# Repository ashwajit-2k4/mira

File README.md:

### EDL 2025 Project Submission Repository.

### Project Name: P-05 : Magnetic Field Camera
### Team Number: MON-08
### Team Members:
- Aditya Vema Reddy Kesari (22b3985)
- Ashwajit Singh (22b1227)
- N V Navaneeth Rajesh (22b1215)
- Raunak Mukherjee (22b3955)
- Suchet Gopal (22b1814)

### Problem Statement and Solution:

<!-- Provide a description about the project and what you've learnt and achieved in this. -->

<b> Problem Statement </b> 

High resolution magnetic imaging of objects is extremely important in industrial applications, to check for defects in manufactured parts like permanent magnets or motors. However, many current products like MAGCAM have exhorbitant costs that make them unviable for many people.

<b> Our Solution </b> 

MIRA M1 fills in this gap, as an affordable  magnetic field camera consisting of an 8x8 sensor array, that maps the field distribution in the volume around an object using an r-theta-z movement rig in just a few minutes. 

The object to be measured is placed on a rotating platform, with the sensor array itself moving in the r-z plane, thus enabling the mapping out of 3D space. The user interacts with a laptop-based GUI, to move the sensors to the starting position, and then start the pre-programmed sweep. The GUI then shows the live heatmap of the values the sensor array sees (at above 80 frames per second), along with a continuously updating scatter plot showing a 3D visualisation of the field.

<b> How It Works </b> 

The GUI starts an SSH connection to a Raspberry Pi, that controls the motors for rig movement, and communicates with the CMOD A7 FPGA that interfaces with the sensor array. When acquisition is started, the RPi rotates the theta motor by 360 degrees in 200 steps, acquiring data from sensors in every step. It then moves in the r direction in steps, repeating this process before it moves up in the z direction.

<b> Deliverables </b> 

- 2mm spatial resolution: **Achieved** (Currently with 1.75mm resolution, which can be increased further)
- 1mT sensitivity: **Achieved** (Obtained 0.2mT sensitivity)

### Key Learnings

Since our project had a lot of moving parts, with the CMOD FPGA, the Raspberry Pi microcontroller and the laptop GUI, in addition to the motor movement mechanism, communication was essential to ensure compatibility between these parts. Additionally, we had to put a lot of thought into component choice, since we could not use commonly available steel components due to interference. Since we required very high resolution, both in terms of magnetic field and spatial movement, it required careful design of PCBs and CAD models, and required adapting parts in the mechanism to ensure that we had minimum spatial error from jitter.

### Walkthrough of the repo

The source code consists of code for 3 devices: CMOD A7 FPGA, Raspberry Pi 5 and the laptop GUI. Additionally, the PCB designs for the sensor PCB we ultimately used, along with the backup PCB, and the PCB containing the FPGA are provided. The CAD models for all 3D printed and laser cut parts are also provided.

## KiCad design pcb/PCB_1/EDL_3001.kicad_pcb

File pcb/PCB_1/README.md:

# TMAG3001 Sensor Array PCB

This repository contains the design files and documentation for the **TMAG3001 Sensor Array PCB**. This is the **main PCB** of the project, designed for high-resolution magnetic field sensing using a dense grid of magnetometers.

## Overview

- **Sensor Type**: TMAG3001 3-axis magnetometers  
- **Array Size**: 8x8 grid (64 sensors)  
- **Inter-sensor Spacing**: 3.5 mm  
- **PCB Type**: 4-layer board  
- **Communication Protocol**: I2C  

---

## Design Details

### I2C Bus Structure

Each group of **4 sensors** forms a **single I2C bus**.  
- Each **TMAG3001** uses **3 I2C lines**: `SCL`, `SDA`, and `INT`.
- A single bus handles 4 sensors, with address selection via the `ADD` pin.
- The `ADD` pin is tied to one of: `VCC`, `GND`, `SCL`, or `SDA` — enabling 4 unique addresses per bus.

> **Note**: To reduce the number of GPIOs, the `INT` lines from every **2 buses are shorted** together.

### Electrical Components

- **Pull-up Resistors**: 1.8 kΩ on all I2C lines  
- **Decoupling Capacitors**:
  - 0.1 µF per IC
  - 2 × 1 µF bulk capacitors at the power input  
- **Power Supply Pins** (per IC): `VCC`, `GND`, `INT`, `SCL`, `SDA`, `ADD`

### Physical Layout

- **IC Placement**: Only TMAG3001 ICs are placed on the **top** layer to avoid magnetic interference.
- **Other Components**: All resistors, capacitors, connectors, etc., are placed on the **bottom** layer.
- **Test Points**: 10 test points on the **bottom** for signal probing and ground testing.

### Grounding and Layer Design

- All 4 layers have **solid ground pours** for noise suppression and signal integrity.

---

## Files & Resources

The repository folders include:
- **Schematic**
- **PCB Layout**
- **3D Renders**
- **Assembled PCB Images**

---

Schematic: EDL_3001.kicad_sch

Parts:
C1, C2, C3, C4, C5, C6, C7, C8, C9, C10, C11, C12, C13, C14, C15, C16, C17, C18, C19, C20, C21, C22, C23, C24, C25, C26, C27, C28, C29, C30, C31, C32, C33, C34, C35, C36, C37, C38, C39, C40, C41, C42, C43, C44, C45, C46, C47, C48, C49, C50, C51, C52, C53, C54, C55, C56, C57, C58, C59, C60, C61, C62, C63, C64: 0.1 u; C_0402_1005Metric
C65, C66: 1 u; C_1206_3216Metric
J1, J2: 524353071; 52435-3071
R1, R2, R3, R4, R5, R6, R7, R8, R9, R10, R11, R12, R13, R14, R15, R16, R17, R18, R19, R20, R21, R22, R23, R24, R25, R26, R27, R28, R29, R30, R31, R32, R33, R34, R35, R36, R37, R38, R39, R40, R41, R42, R43, R44, R45, R46, R47, R48: 1.8k; R_0402_1005Metric
TP1, TP2, TP3, TP4, TP5, TP6, TP7, TP8, TP9, TP10: TestPoint; TestPoint_Plated_Hole_D2.0mm
U1, U2, U3, U4, U5, U6, U7, U8, U9, U10, U11, U12, U13, U14, U15, U16, U17, U18, U19, U20, U21, U22, U23, U24, U25, U26, U27, U28, U29, U30, U31, U32, U33, U34, U35, U36, U37, U38, U39, U40, U41, U42, U43, U44, U45, U46, U47, U48, U49, U50, U51, U52, U53, U54, U55, U56, U57, U58, U59, U60, U61, U62, U63, U64: TMAG3001A2YBGR; DSBGA6_YBG_TEX

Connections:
GND: C1.2, C2.2, C3.2, C4.2, C5.2, C6.2, C7.2, C8.2, C9.2, C10.2, C11.2, C12.2, C13.2, C14.2, C15.2, C16.2, C17.2, C18.2, C19.2, C20.2, C21.2, C22.2, C23.2, C24.2, C25.2, C26.2, C27.2, C28.2, C29.2, C30.2, C31.2, C32.2, C33.2, C34.2, C35.2, C36.2, C37.2, C38.2, C39.2, C40.2, C41.2, C42.2, C43.2, C44.2, C45.2, C46.2, C47.2, C48.2, C49.2, C50.2, C51.2, C52.2, C53.2, C54.2, C55.2, C56.2, C57.2, C58.2, C59.2, C60.2, C61.2, C62.2, C63.2, C64.2, C65.2, C66.2, J1.1, J1.2, J1.3, J1.4, J1.5, J1.6, J1.7, J1.8, J1.9, J1.10, J1.31, J1.32, J2.21, J2.22, J2.23, J2.24, J2.25, J2.27, J2.29, J2.30, J2.31, J2.32, TP9.1, TP10.1, U1.B2 (GND), U2.A2 (ADDR), U2.B2 (GND), U3.B2 (GND), U4.B2 (GND), U5.B2 (GND), U6.A2 (ADDR), U6.B2 (GND), U7.B2 (GND), U8.B2 (GND), U9.B2 (GND), U10.A2 (ADDR), U10.B2 (GND), U11.B2 (GND), U12.B2 (GND), U13.B2 (GND), U14.A2 (ADDR), U14.B2 (GND), U15.B2 (GND), U16.B2 (GND), U17.B2 (GND), U18.A2 (ADDR), U18.B2 (GND), U19.B2 (GND), U20.B2 (GND), U21.B2 (GND), U22.A2 (ADDR), U22.B2 (GND), U23.B2 (GND), U24.B2 (GND), U25.B2 (GND), U26.A2 (ADDR), U26.B2 (GND), U27.B2 (GND), U28.B2 (GND), U29.B2 (GND), U30.A2 (ADDR), U30.B2 (GND), U31.B2 (GND), U32.B2 (GND), U33.B2 (GND), U34.A2 (ADDR), U34.B2 (GND), U35.B2 (GND), U36.B2 (GND), U37.B2 (GND), U38.A2 (ADDR), U38.B2 (GND), U39.B2 (GND), U40.B2 (GND), U41.B2 (GND), U42.A2 (ADDR), U42.B2 (GND), U43.B2 (GND), U44.B2 (GND), U45.B2 (GND), U46.A2 (ADDR), U46.B2 (GND), U47.B2 (GND), U48.B2 (GND), U49.B2 (GND), U50.A2 (ADDR), U50.B2 (GND), U51.B2 (GND), U52.B2 (GND), U53.B2 (GND), U54.A2 (ADDR), U54.B2 (GND), U55.B2 (GND), U56.B2 (GND), U57.B2 (GND), U58.A2 (ADDR), U58.B2 (GND), U59.B2 (GND), U60.B2 (GND), U61.B2 (GND), U62.A2 (ADDR), U62.B2 (GND), U63.B2 (GND), U64.B2 (GND)
unnamed: R33.2, R34.1
unnamed: R35.2, R36.1
unnamed: R37.2, R38.1
unnamed: R39.2, R40.1
unnamed: R41.2, R42.1
unnamed: R43.2, R44.1
unnamed: R45.2, R46.1
unnamed: R47.2, R48.1
unnamed: J1.30, R34.2, U1.B1 (*INT), U2.B1 (*INT), U3.B1 (*INT), U4.B1 (*INT), U5.B1 (*INT), U6.B1 (*INT), U7.B1 (*INT), U8.B1 (*INT)
unnamed: J1.29, R1.2, U1.C2 (SCL), U2.C2 (SCL), U3.C2 (SCL), U4.A2 (ADDR), U4.C2 (SCL)
unnamed: J1.28, R2.2, U1.C1 (SDA), U2.C1 (SDA), U3.A2 (ADDR), U3.C1 (SDA), U4.C1 (SDA)
unnamed: J1.27, R3.2, U5.C2 (SCL), U6.C2 (SCL), U7.C2 (SCL), U8.A2 (ADDR), U8.C2 (SCL)
unnamed: J1.26, R4.2, U5.C1 (SDA), U6.C1 (SDA), U7.A2 (ADDR), U7.C1 (SDA), U8.C1 (SDA)
unnamed: J1.25, R36.2, U9.B1 (*INT), U10.B1 (*INT), U11.B1 (*INT), U12.B1 (*INT), U13.B1 (*INT), U14.B1 (*INT), U15.B1 (*INT), U16.B1 (*INT)
unnamed: J1.24, R5.2, U9.C2 (SCL), U10.C2 (SCL), U11.C2 (SCL), U12.A2 (ADDR), U12.C2 (SCL)
unnamed: J1.23, R6.2, U9.C1 (SDA), U10.C1 (SDA), U11.A2 (ADDR), U11.C1 (SDA), U12.C1 (SDA)
unnamed: J1.22, R7.2, U13.C2 (SCL), U14.C2 (SCL), U15.C2 (SCL), U16.A2 (ADDR), U16.C2 (SCL)
unnamed: J1.21, R8.2, U13.C1 (SDA), U14.C1 (SDA), U15.A2 (ADDR), U15.C1 (SDA), U16.C1 (SDA)
unnamed: J1.20, R38.2, U17.B1 (*INT), U18.B1 (*INT), U19.B1 (*INT), U20.B1 (*INT), U21.B1 (*INT), U22.B1 (*INT), U23.B1 (*INT), U24.B1 (*INT)
unnamed: J1.19, R9.2, U17.C2 (SCL), U18.C2 (SCL), U19.C2 (SCL), U20.A2 (ADDR), U20.C2 (SCL)
unnamed: J1.18, R10.2, U17.C1 (SDA), U18.C1 (SDA), U19.A2 (ADDR), U19.C1 (SDA), U20.C1 (SDA)
unnamed: J1.17, R11.2, U21.C2 (SCL), U22.C2 (SCL), U23.C2 (SCL), U24.A2 (ADDR), U24.C2 (SCL)
unnamed: J1.16, R12.2, U21.C1 (SDA), U22.C1 (SDA), U23.A2 (ADDR), U23.C1 (SDA), U24.C1 (SDA)
unnamed: J1.15, R40.2, TP1.1, U25.B1 (*INT), U26.B1 (*INT), U27.B1 (*INT), U28.B1 (*INT), U29.B1 (*INT), U30.B1 (*INT), U31.B1 (*INT), U32.B1 (*INT)
unnamed: J1.14, R13.2, U25.C2 (SCL), U26.C2 (SCL), U27.C2 (SCL), U28.A2 (ADDR), U28.C2 (SCL)
unnamed: J1.13, R14.2, U25.C1 (SDA), U26.C1 (SDA), U27.A2 (ADDR), U27.C1 (SDA), U28.C1 (SDA)
unnamed: J1.12, R15.2, TP2.1, U29.C2 (SCL), U30.C2 (SCL), U31.C2 (SCL), U32.A2 (ADDR), U32.C2 (SCL)
unnamed: J1.11, R16.2, TP3.1, U29.C1 (SDA), U30.C1 (SDA), U31.A2 (ADDR), U31.C1 (SDA), U32.C1 (SDA)
unnamed: J2.1, R42.2, U33.B1 (*INT), U34.B1 (*INT), U35.B1 (*INT), U36.B1 (*INT), U37.B1 (*INT), U38.B1 (*INT), U39.B1 (*INT), U40.B1 (*INT)
unnamed: J2.2, R17.2, U33.C2 (SCL), U34.C2 (SCL), U35.C2 (SCL), U36.A2 (ADDR), U36.C2 (SCL)
unnamed: J2.3, R18.2, U33.C1 (SDA), U34.C1 (SDA), U35.A2 (ADDR), U35.C1 (SDA), U36.C1 (SDA)
unnamed: J2.4, R19.2, U37.C2 (SCL), U38.C2 (SCL), U39.C2 (SCL), U40.A2 (ADDR), U40.C2 (SCL)
unnamed: J2.5, R20.2, U37.C1 (SDA), U38.C1 (SDA), U39.A2 (ADDR), U39.C1 (SDA), U40.C1 (SDA)
unnamed: J2.6, R44.2, U41.B1 (*INT), U42.B1 (*INT), U43.B1 (*INT), U44.B1 (*INT), U45.B1 (*INT), U46.B1 (*INT), U47.B1 (*INT), U48.B1 (*INT)
unnamed: J2.7, R21.2, U41.C2 (SCL), U42.C2 (SCL), U43.C2 (SCL), U44.A2 (ADDR), U44.C2 (SCL)
unnamed: J2.8, R22.2, U41.C1 (SDA), U42.C1 (SDA), U43.A2 (ADDR), U43.C1 (SDA), U44.C1 (SDA)
unnamed: J2.9, R23.2, U45.C2 (SCL), U46.C2 (SCL), U47.C2 (SCL), U48.A2 (ADDR), U48.C2 (SCL)
unnamed: J2.10, R24.2, U45.C1 (SDA), U46.C1 (SDA), U47.A2 (ADDR), U47.C1 (SDA), U48.C1 (SDA)
unnamed: J2.11, R46.2, U49.B1 (*INT), U50.B1 (*INT), U51.B1 (*INT), U52.B1 (*INT), U53.B1 (*INT), U54.B1 (*INT), U55.B1 (*INT), U56.B1 (*INT)
unnamed: J2.12, R25.2, U49.C2 (SCL), U50.C2 (SCL), U51.C2 (SCL), U52.A2 (ADDR), U52.C2 (SCL)
unnamed: J2.13, R26.2, U49.C1 (SDA), U50.C1 (SDA), U51.A2 (ADDR), U51.C1 (SDA), U52.C1 (SDA)
unnamed: J2.14, R27.2, U53.C2 (SCL), U54.C2 (SCL), U55.C2 (SCL), U56.A2 (ADDR), U56.C2 (SCL)
unnamed: J2.15, R28.2, U53.C1 (SDA), U54.C1 (SDA), U55.A2 (ADDR), U55.C1 (SDA), U56.C1 (SDA)
unnamed: J2.16, R48.2, TP4.1, U57.B1 (*INT), U58.B1 (*INT), U59.B1 (*INT), U60.B1 (*INT), U61.B1 (*INT), U62.B1 (*INT), U63.B1 (*INT), U64.B1 (*INT)
unnamed: J2.17, R29.2, U57.C2 (SCL), U58.C2 (SCL), U59.C2 (SCL), U60.A2 (ADDR), U60.C2 (SCL)
unnamed: J2.18, R30.2, U57.C1 (SDA), U58.C1 (SDA), U59.A2 (ADDR), U59.C1 (SDA), U60.C1 (SDA)
unnamed: J2.19, R31.2, TP5.1, U61.C2 (SCL), U62.C2 (SCL), U63.C2 (SCL), U64.A2 (ADDR), U64.C2 (SCL)
unnamed: J2.20, R32.2, TP6.1, U61.C1 (SDA), U62.C1 (SDA), U63.A2 (ADDR), U63.C1 (SDA), U64.C1 (SDA)
VCC: C1.1, C2.1, C3.1, C4.1, C5.1, C6.1, C7.1, C8.1, C9.1, C10.1, C11.1, C12.1, C13.1, C14.1, C15.1, C16.1, C17.1, C18.1, C19.1, C20.1, C21.1, C22.1, C23.1, C24.1, C25.1, C26.1, C27.1, C28.1, C29.1, C30.1, C31.1, C32.1, C66.1, J2.28, R1.1, R2.1, R3.1, R4.1, R5.1, R6.1, R7.1, R8.1, R9.1, R10.1, R11.1, R12.1, R13.1, R14.1, R15.1, R16.1, R33.1, R35.1, R37.1, R39.1, TP7.1, U1.A1 (VCC), U1.A2 (ADDR), U2.A1 (VCC), U3.A1 (VCC), U4.A1 (VCC), U5.A1 (VCC), U5.A2 (ADDR), U6.A1 (VCC), U7.A1 (VCC), U8.A1 (VCC), U9.A1 (VCC), U9.A2 (ADDR), U10.A1 (VCC), U11.A1 (VCC), U12.A1 (VCC), U13.A1 (VCC), U13.A2 (ADDR), U14.A1 (VCC), U15.A1 (VCC), U16.A1 (VCC), U17.A1 (VCC), U17.A2 (ADDR), U18.A1 (VCC), U19.A1 (VCC), U20.A1 (VCC), U21.A1 (VCC), U21.A2 (ADDR), U22.A1 (VCC), U23.A1 (VCC), U24.A1 (VCC), U25.A1 (VCC), U25.A2 (ADDR), U26.A1 (VCC), U27.A1 (VCC), U28.A1 (VCC), U29.A1 (VCC), U29.A2 (ADDR), U30.A1 (VCC), U31.A1 (VCC), U32.A1 (VCC)
VCC2: C33.1, C34.1, C35.1, C36.1, C37.1, C38.1, C39.1, C40.1, C41.1, C42.1, C43.1, C44.1, C45.1, C46.1, C47.1, C48.1, C49.1, C50.1, C51.1, C52.1, C53.1, C54.1, C55.1, C56.1, C57.1, C58.1, C59.1, C60.1, C61.1, C62.1, C63.1, C64.1, C65.1, J2.26, R17.1, R18.1, R19.1, R20.1, R21.1, R22.1, R23.1, R24.1, R25.1, R26.1, R27.1, R28.1, R29.1, R30.1, R31.1, R32.1, R41.1, R43.1, R45.1, R47.1, TP8.1, U33.A1 (VCC), U33.A2 (ADDR), U34.A1 (VCC), U35.A1 (VCC), U36.A1 (VCC), U37.A1 (VCC), U37.A2 (ADDR), U38.A1 (VCC), U39.A1 (VCC), U40.A1 (VCC), U41.A1 (VCC), U41.A2 (ADDR), U42.A1 (VCC), U43.A1 (VCC), U44.A1 (VCC), U45.A1 (VCC), U45.A2 (ADDR), U46.A1 (VCC), U47.A1 (VCC), U48.A1 (VCC), U49.A1 (VCC), U49.A2 (ADDR), U50.A1 (VCC), U51.A1 (VCC), U52.A1 (VCC), U53.A1 (VCC), U53.A2 (ADDR), U54.A1 (VCC), U55.A1 (VCC), U56.A1 (VCC), U57.A1 (VCC), U57.A2 (ADDR), U58.A1 (VCC), U59.A1 (VCC), U60.A1 (VCC), U61.A1 (VCC), U61.A2 (ADDR), U62.A1 (VCC), U63.A1 (VCC), U64.A1 (VCC)

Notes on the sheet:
MAGNETOMETER ARRAY (8X8)
Power Supply

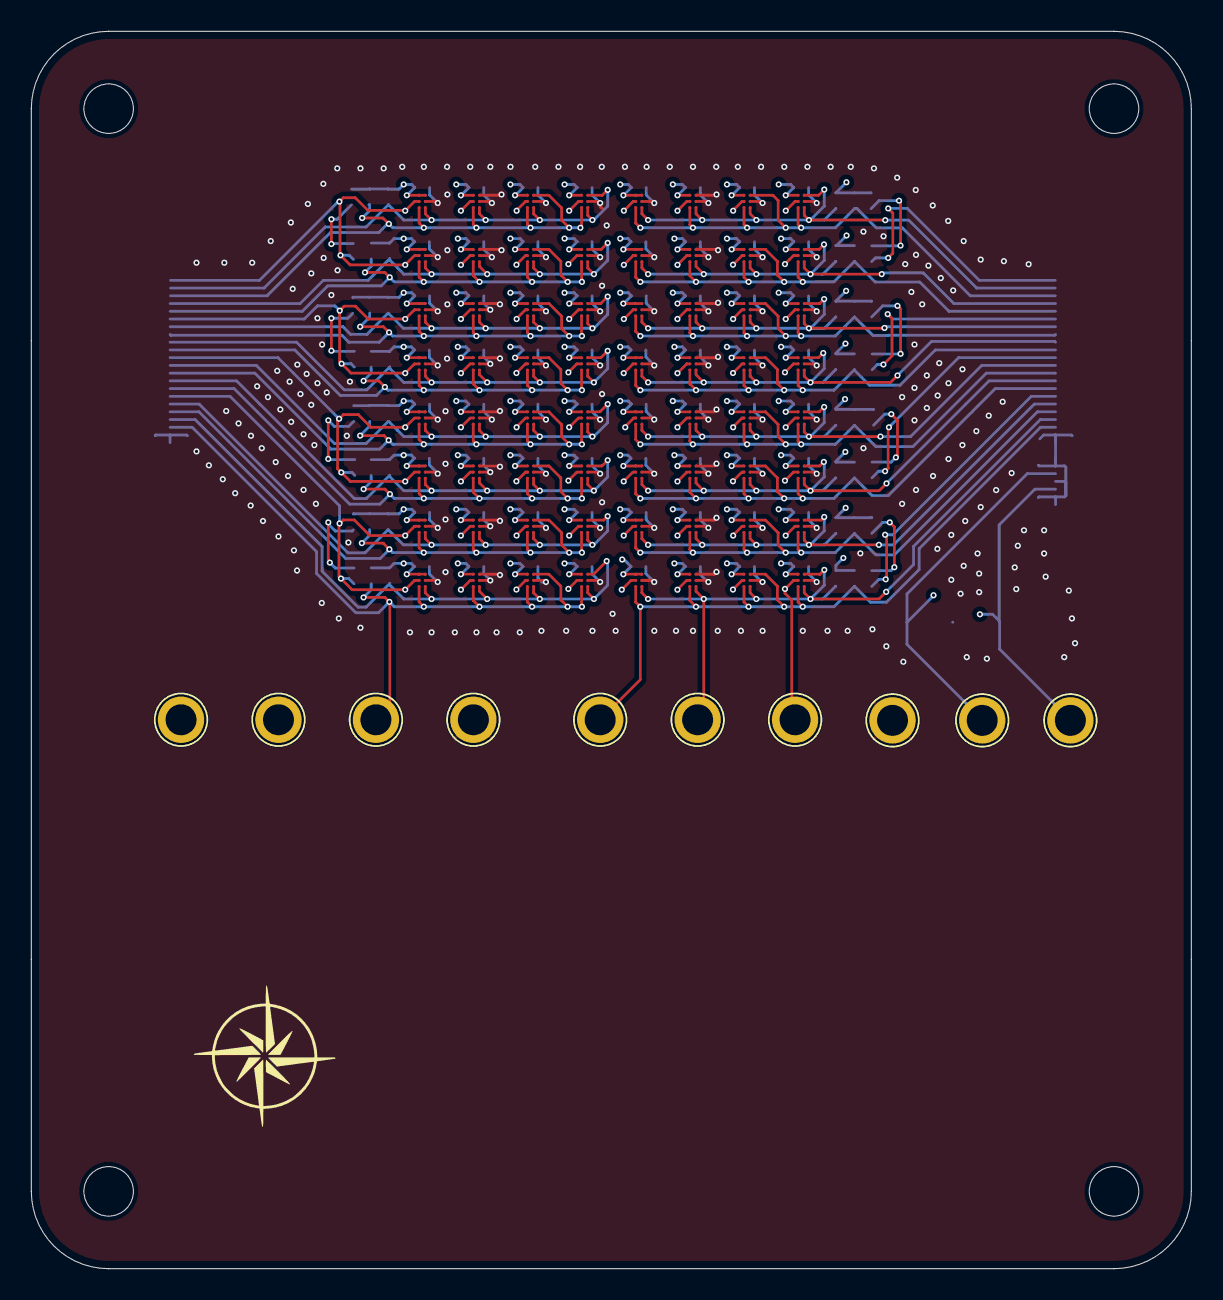
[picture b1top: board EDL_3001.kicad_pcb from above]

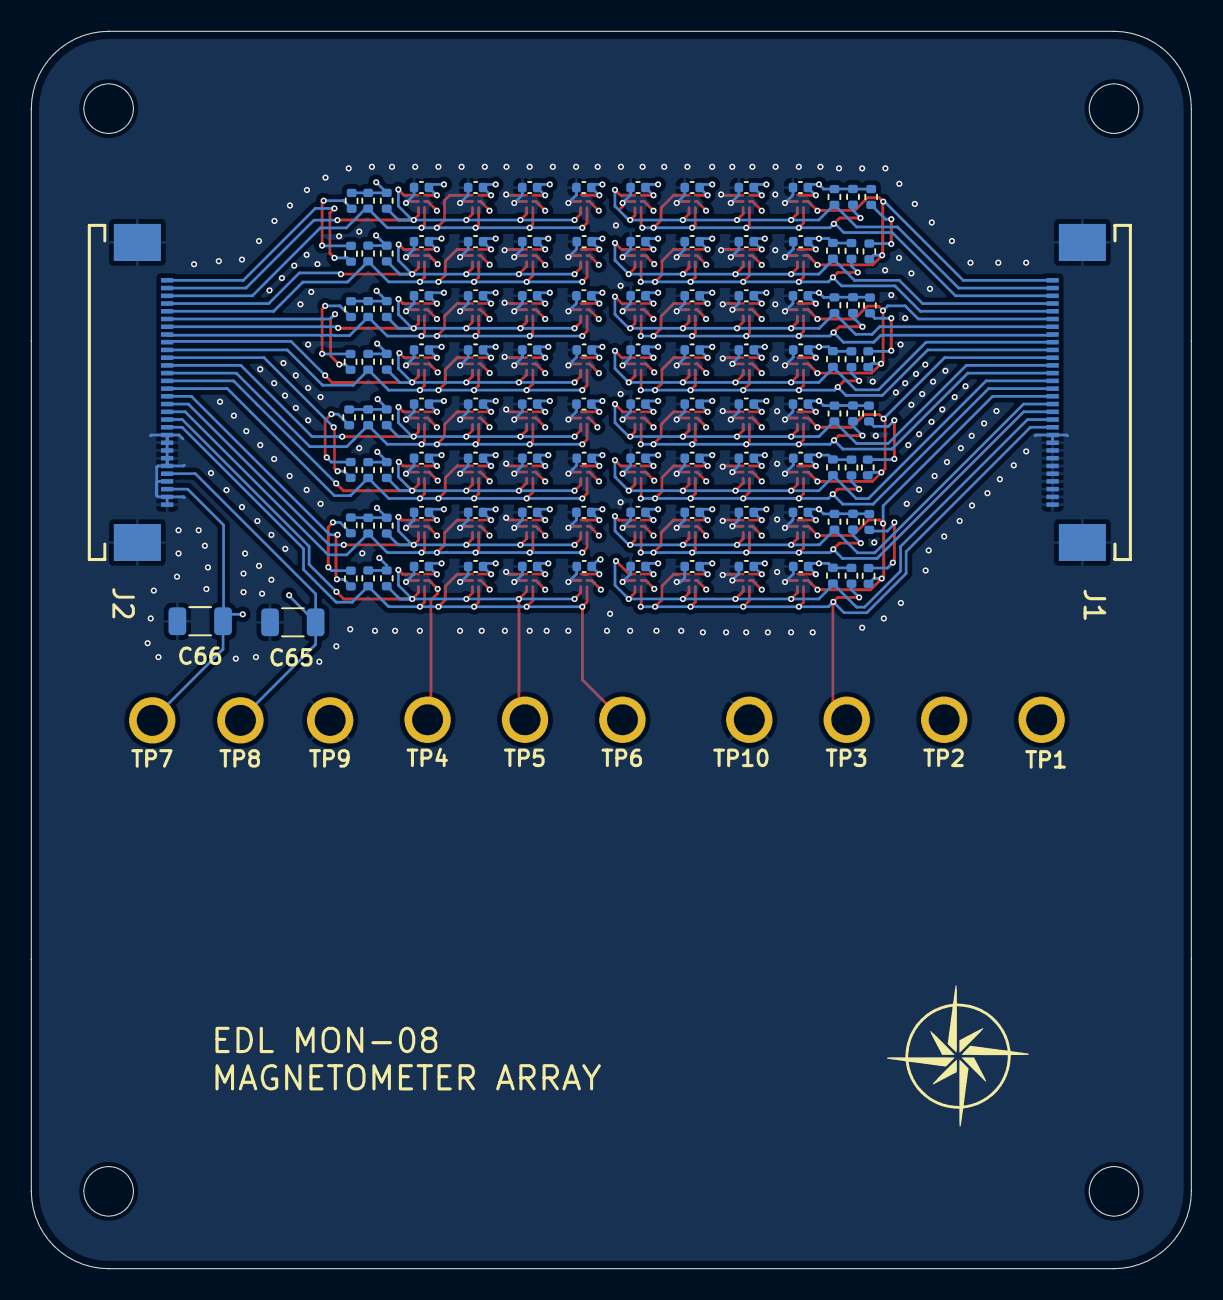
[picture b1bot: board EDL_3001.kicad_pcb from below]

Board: 4 copper layers, 75.0 x 80.0 mm, 190 parts (116 on the bottom side), 51 nets.
